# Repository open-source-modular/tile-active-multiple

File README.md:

# tile-active-multiple

An active multiple tile with one input and three outputs.

This tile uses stereo mini jack connectors, since they are cheaper than the mono version.
The middle pin is purposely not connected.

KiCAD files are for version 6.

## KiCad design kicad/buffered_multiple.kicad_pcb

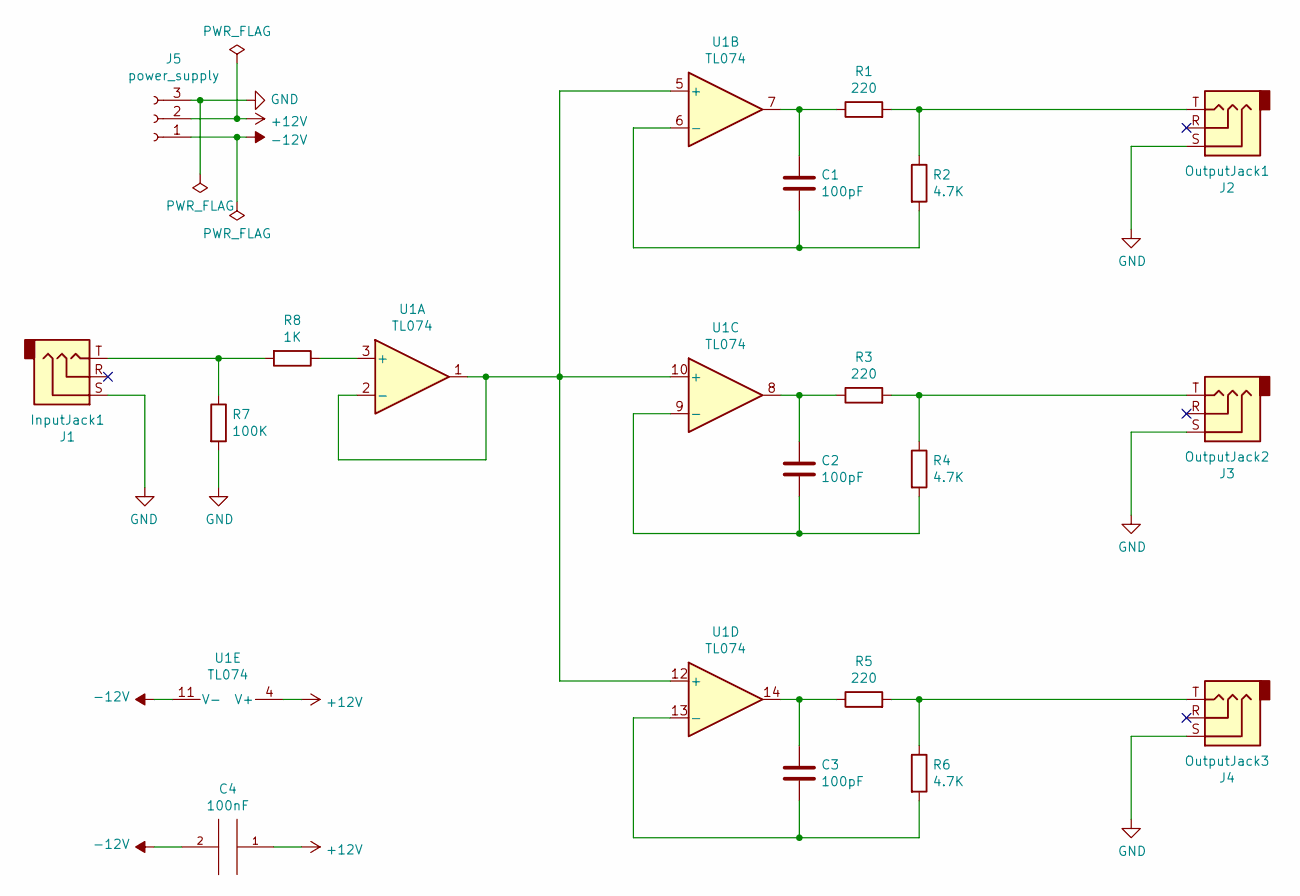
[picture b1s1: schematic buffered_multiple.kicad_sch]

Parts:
C1, C2, C3: 100pF; C_1206_HandSoldering
C4: 100nF; C_1206_HandSoldering
J1: InputJack1; PJ392-3.5mm-jack-vertical-SRT
J2: OutputJack1; PJ392-3.5mm-jack-vertical-SRT
J3: OutputJack2; PJ392-3.5mm-jack-vertical-SRT
J4: OutputJack3; PJ392-3.5mm-jack-vertical-SRT
J5: power_supply; eurorack-tile-power-connector
R1, R3, R5: 220; R_1206_HandSoldering
R2, R4, R6: 4.7K; R_1206_HandSoldering
R7: 100K; R_1206_HandSoldering
R8: 1K; R_1206_HandSoldering
U1: TL074; SOIC-14_N

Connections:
+12V: C4.1, J5.2, U1.4 (V+)
-12V: C4.2, J5.1, U1.11 (V-)
GND: J1.S, J2.S, J3.S, J4.S, J5.3, R7.2
unnamed: C1.1, R1.1, U1.7
unnamed: C1.2, R2.2, U1.6 (-)
unnamed: C2.1, R3.1, U1.8
unnamed: C2.2, R4.2, U1.9 (-)
unnamed: C3.1, R5.1, U1.14
unnamed: C3.2, R6.2, U1.13 (-)
unnamed: J1.T, R7.1, R8.2
unnamed: J2.T, R1.2, R2.1
unnamed: J3.T, R3.2, R4.1
unnamed: J4.T, R5.2, R6.1
unnamed: R8.1, U1.3 (+)
unnamed: U1.1, U1.2 (-), U1.5 (+), U1.10 (+), U1.12 (+)

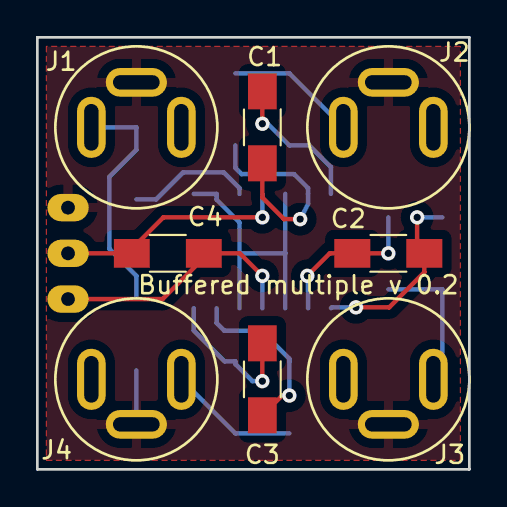
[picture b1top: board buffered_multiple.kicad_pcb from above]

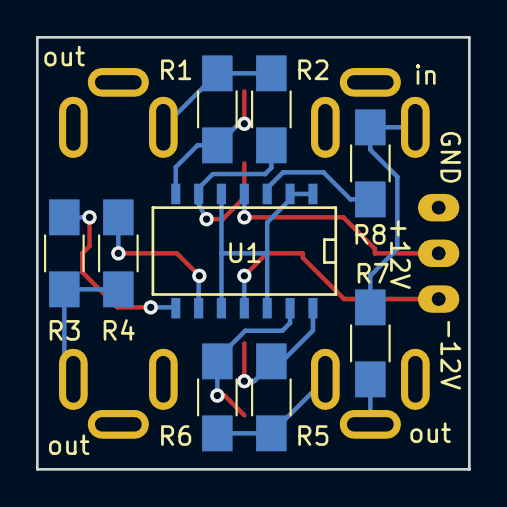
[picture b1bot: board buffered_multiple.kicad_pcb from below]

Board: 2 copper layers, 24.0 x 24.0 mm, 18 parts (9 on the bottom side), 15 nets.

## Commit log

2022-10-10 Changed format of KiCAD files from v5 to v6
2022-10-10 Added Gerber files
2022-10-10 Ignore KiCAD auto saves
2022-10-10 Added renders of PCB
2022-10-11 Footprints submodules now uses SSH, not HTTPS
2022-10-11 Correct footprint for power. One resistor was connected wrong way
2022-10-11 Moved component references so they are visible on populated board
2022-10-11 Added gerbers for updated PCB
